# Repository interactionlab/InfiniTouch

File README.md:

# InfiniTouch: Finger-Aware Interaction on Fully Touch Sensitive Smartphones
This repository contains both the hardware models and specifications for the full-touch smartphone prototype presented in the paper, 
as well as scripts and the model for estimating 3D finger positions on the device as described in the paper. 
Moreover, our dataset can be downloaded in the link provided below.

## Abstract
Smartphones are the most successful mobile devices and offer intuitive interaction through touchscreens. Current devices
treat all fingers equally and only sense touch contacts on the front of the device. In this paper, we present InfiniTouch,
the first system that enables touch input on the whole device surface and identifies the fingers touching the device without
external sensors while keeping the form factor of a standard smartphone. We first developed a prototype with capacitive
sensors on the front, the back and on three sides. We then conducted a study to train a convolutional neural network that
identifies fingers with an accuracy of 95.78% while estimating their position with a mean absolute error of 0.74cm . We
demonstrate the usefulness of multiple use cases made possible with InfiniTouch, including finger-aware gestures and finger
flexion state as an action modifier.

This work can be cited as follows:
<pre>
@inproceedings{le2018infinitouch,
 author = {Le, Huy Viet and  Mayer, Sven and Henze, Niels},
 title = {InfiniTouch: Finger-Aware Interaction on Fully Touch Sensitive Smartphones},
 booktitle = {Proceedings of the 31th Annual ACM Symposium on User Interface Software and Technology},
 series = {UIST '18},
 year = {2018},
 isbn = {978-1-4503-5948-1},
 doi = {10.1145/3242587.3242605},
 url = {http://doi.acm.org/10.1145/3242587.3242605},
 location = {Berlin, Germany},
 numpages = {14},
 publisher = {ACM},
 address = {New York, NY, USA}
} 
</pre>

## Dataset
The dataset can be downloaded at: https://www.dropbox.com/s/v8n8uaf5vncusyn/InfiniTouch_Dataset.zip?dl=0. After downloading, place the content of this folder into a folder named 'data'. Place the 'data' folder into the same directory as the Jupyter notebooks. Run the content of these notebooks to create a HDF5 file with which the model can then be trained.

## Prototype
The datasheets of the components that we used in our prototype can be found in the following list of URLs:
- BM10NB(0.8)-40DS-0.4V(51): https://www.datasheets360.com/part/detail/bm10nb-0-8-40ds-0-4v-51/2579290684464631510/
- BM10B(0.8)-40DP-0.4V(51): https://www.datasheets360.com/part/detail/bm10b-0-8-40dp-0-4v-51/-1995328425388918022/
- MPR121QR2: https://www.datasheets360.com/part/detail/mpr121qr2/3714073967749496703/
- MicroUSB Breakout Board: https://cdn-shop.adafruit.com/datasheets/1833_MicroB_20329.pdf
- Tactile Switch: https://cdn-shop.adafruit.com/datasheets/B3F-1000-Omron.pdf
- FH12-50S-0.5SH(05): https://www.datasheets360.com/part/detail/fh12-50s-0-5sh-05/8224149447061018923/
- PCB board + FFC cable: http://diy.shops.hypeltd.com/DIY2//product_info.php?products_id=67

We printed the PCB and placed the components on the board with the service of http://beta-layout.com.

## Android Library
To use the library, include libftsp.jar in your Android project. The capacitive images for the local device can be accessed as follows:
```java
LocalDeviceHandler localDeviceHandler = new LocalDeviceHandler();
localDeviceHandler.setLocalCapImgListener(new LocalCapImgListener() {
    @Override
    public void onLocalCapImg(CapacitiveImageTS capImg) { // called approximately every 50ms
        int[][] matrix = capImg.getMatrix(); // get the 27x15 capacitive image
        int[] flattenedMatrix = capImg.getFlattenedMatrix(); // get a flattened 27x15 capacitive image
        long imgTimestamp = capImg.getTimestamp(); // get timestamp of this image
    }
});
localDeviceHandler.startHandler();
```

The following code is for the front unit. It provides the capacitive images of the front device (local) and further the retrieved capacitive imags of the back and the sides. All capacitive images can be retrieved within callbacks:

```java
try {
    frontDeviceHandler = new FrontDeviceHandler(9584);
} catch (SocketException e) {
    e.printStackTrace();
}

frontDeviceHandler.setFtspCapImgListener(new FTSPCapImgListener() {
    @Override
    public void onNewBackCapacitiveImage(CapacitiveImageTS capacitiveImageTS) {
        // backImage = capacitiveImageTS;
    }

    @Override
    public void onNewFrontCapacitiveImage(CapacitiveImageTS capacitiveImageTS) {
        // frontImage = capacitiveImageTS;
    }

    @Override
    public void onNewSideCapacitiveImage(CapacitiveImageSide capacitiveImageSide) {
        // sideImage = capacitiveImageSide;
    }
});
frontDeviceHandler.startHandler(true);
```

The back unit uses the respective code to broadcast the capacitive images to the front unit. A callback handler can also be added if required.
```java
backDeviceHandler = new BackDeviceHandler(Constants.FRONT_IP, 9584);
backDeviceHandler.startHandler(true);
```

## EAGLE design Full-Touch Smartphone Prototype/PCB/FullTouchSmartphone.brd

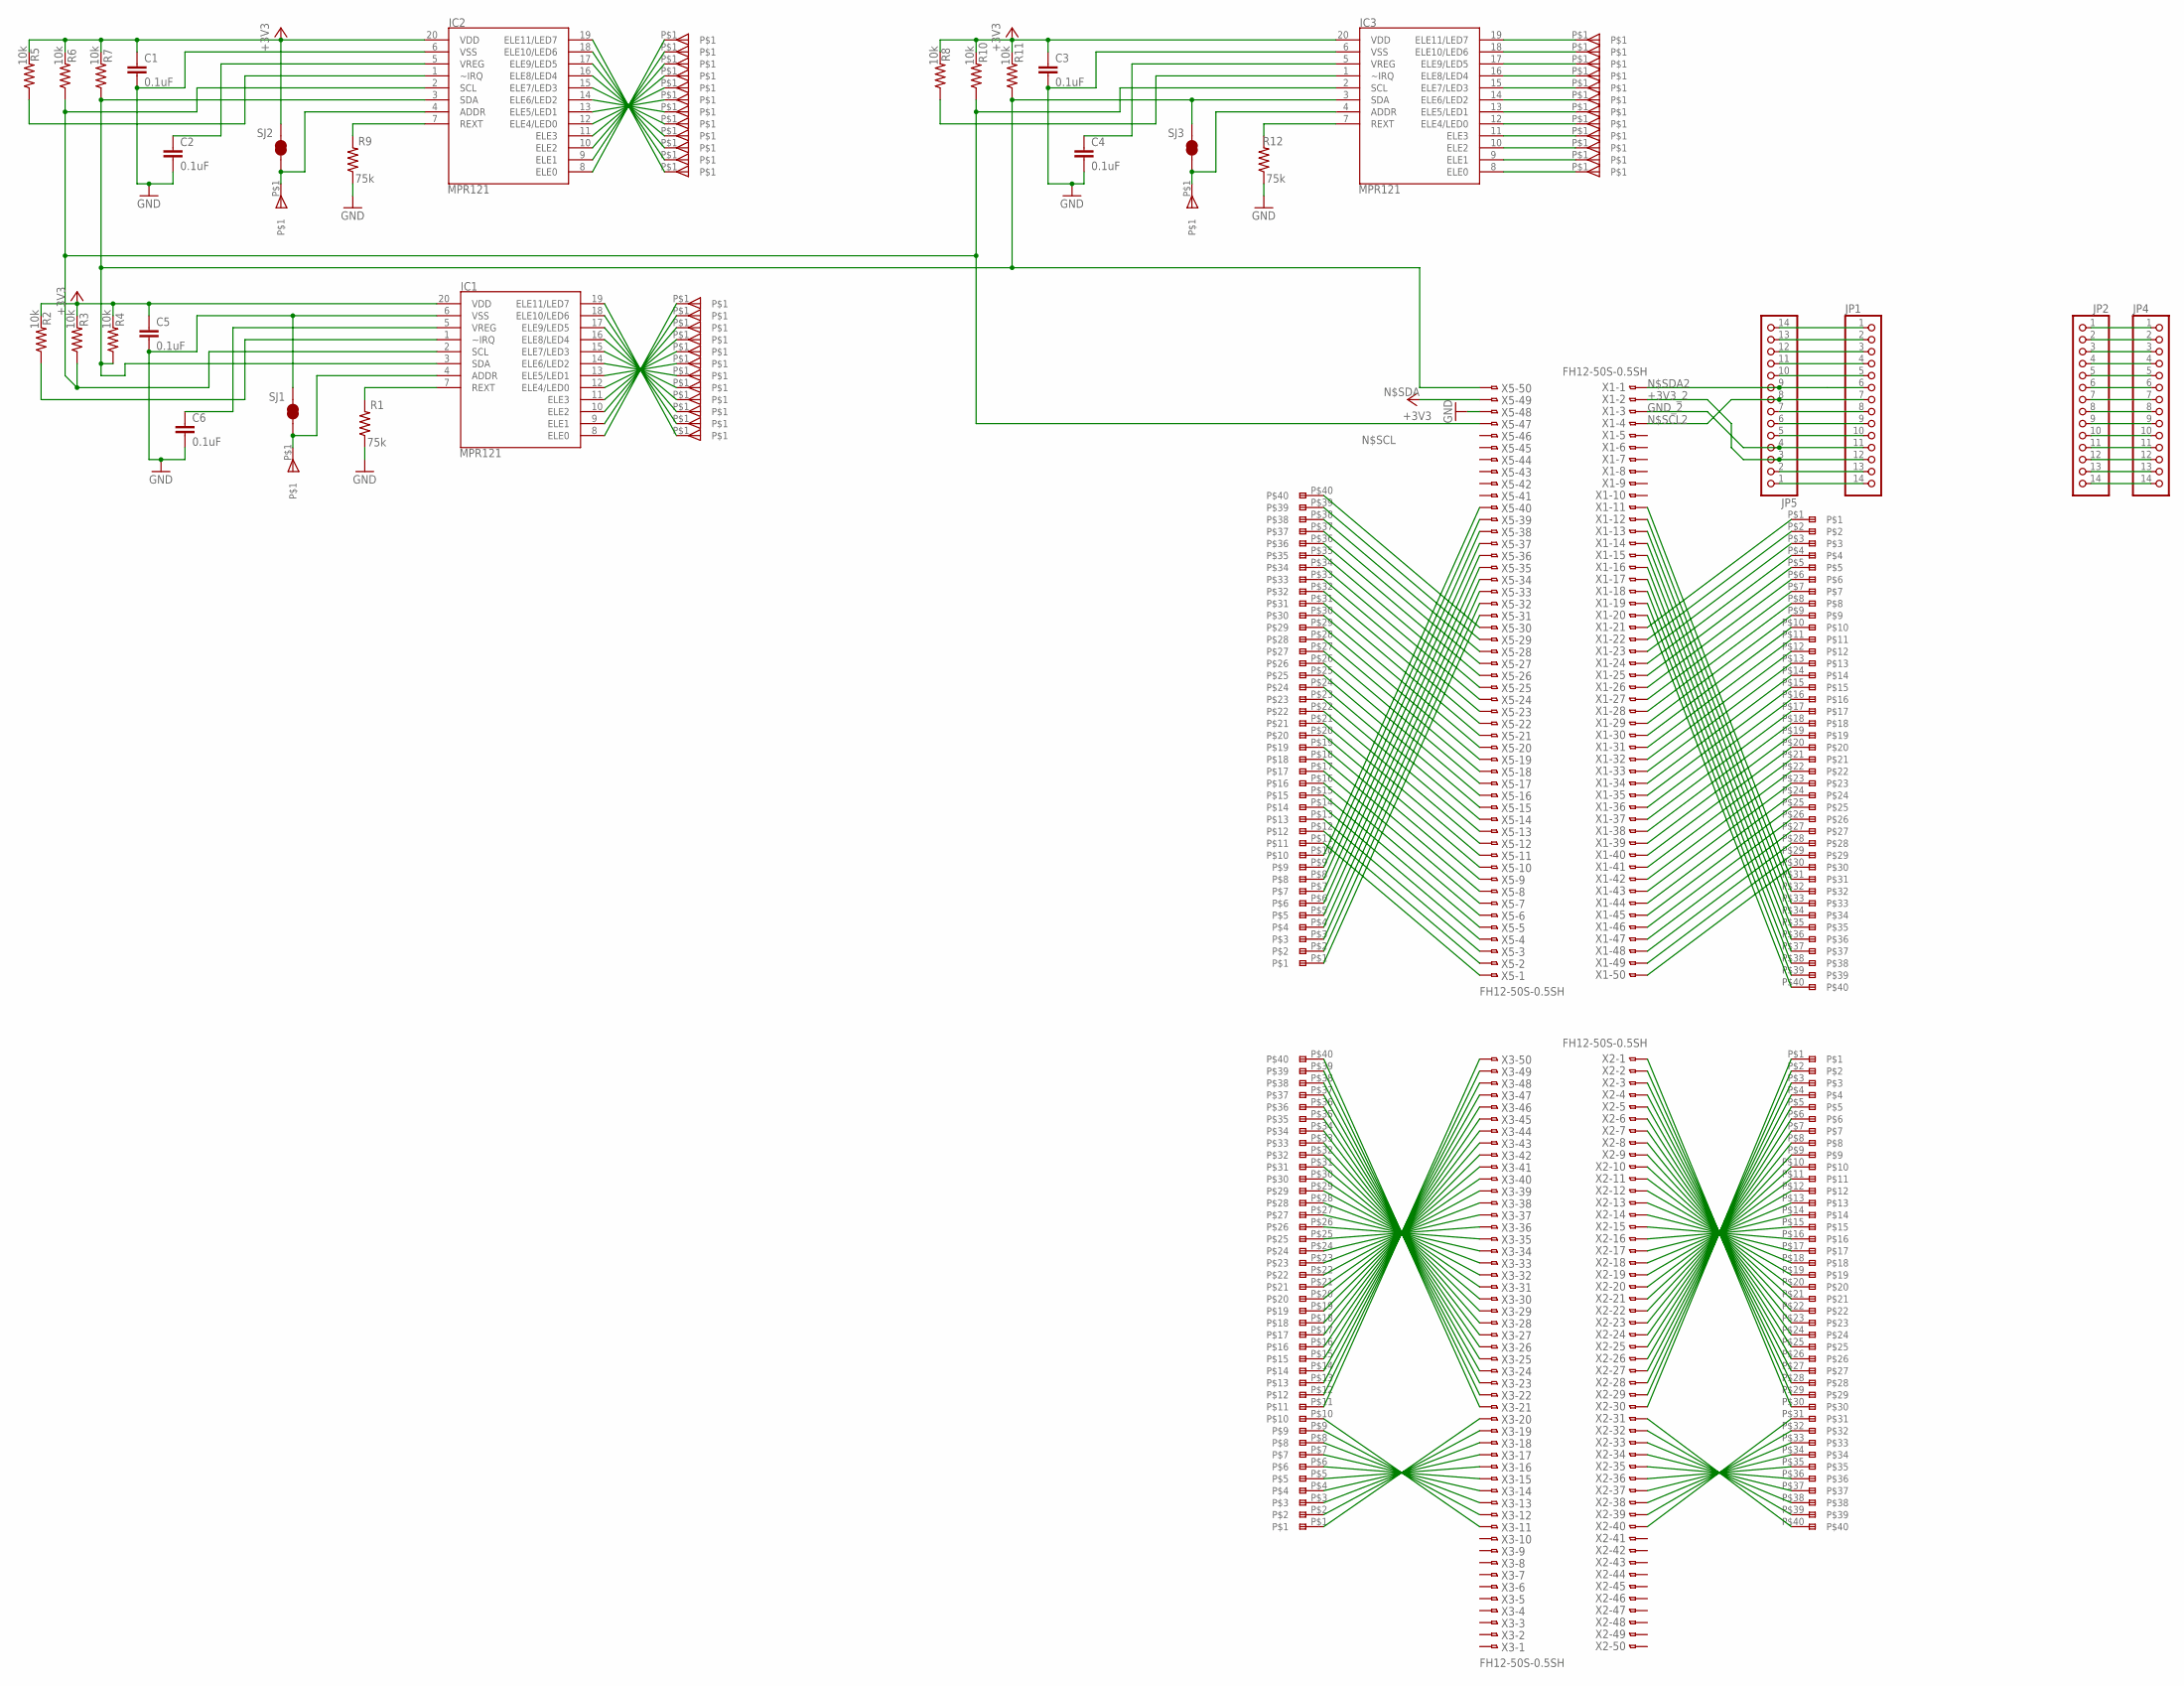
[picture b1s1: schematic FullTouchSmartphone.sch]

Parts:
C1, C2, C3, C4, C5, C6: 0.1uF; 0603-CAP
IC1, IC2, IC3: MPR121; QFN-20-0.4MM-V2
JP1, JP2, JP4, JP5: PINHD-1X14; 1X14
R1, R9, R12: 75k; 0603-RES
R2, R3, R4, R5, R6, R7, R8, R10, R11: 10k; 0603-RES
SJ1, SJ2, SJ3: SOLDERJUMPERTRACE; SJ_2S-TRACE
U$1, U$2: AXE640124
U$3, U$40PIN-BACK: AXE540127
U$4, U$5, U$6, U$7, U$8, U$9, U$10, U$11, U$12, U$13, U$14, U$15, U$25, U$26, U$27, U$28, U$29, U$30, U$31, U$32, U$33, U$34, U$35, U$36, U$37, U$38, U$39, U$40, U$41, U$42, U$43, U$44, U$45, U$46, U$47, U$48, U$49, U$50, U$51: SINGLE_LÖT_SPOT_K
X1, X2, X3, X5: FH12-50S-0.5SH

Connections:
+3V3: C1.1, C3.1, C5.1, IC1.20 (VDD), IC2.20 (VDD), IC3.20 (VDD), R2.2, R3.2, R4.2, R5.2, R6.2, R7.2, R8.2, R10.2, R11.2, SJ2.2, X5.49
+3V3_2: JP1.12, JP5.3, X1.2
GND: C1.2, C2.2, C3.2, C4.2, C5.2, C6.2, IC1.6 (VSS), IC2.6 (VSS), IC3.6 (VSS), R1.1, R9.1, R12.1, SJ1.2, X5.48
GND_2: JP1.11, JP5.4, X1.3
unnamed: U$40PIN-BACK.P$10, X5.40
unnamed: U$40PIN-BACK.P$9, X5.39
unnamed: U$40PIN-BACK.P$8, X5.38
unnamed: U$40PIN-BACK.P$7, X5.37
unnamed: U$40PIN-BACK.P$6, X5.36
unnamed: U$40PIN-BACK.P$5, X5.35
unnamed: U$40PIN-BACK.P$4, X5.34
unnamed: U$40PIN-BACK.P$3, X5.33
unnamed: U$40PIN-BACK.P$2, X5.32
unnamed: U$40PIN-BACK.P$1, X5.31
unnamed: U$40PIN-BACK.P$20, X5.10
unnamed: U$40PIN-BACK.P$19, X5.9
unnamed: U$40PIN-BACK.P$18, X5.8
unnamed: U$40PIN-BACK.P$17, X5.7
unnamed: U$40PIN-BACK.P$16, X5.6
unnamed: U$40PIN-BACK.P$15, X5.5
unnamed: U$40PIN-BACK.P$14, X5.4
unnamed: U$40PIN-BACK.P$13, X5.3
unnamed: U$40PIN-BACK.P$12, X5.2
unnamed: U$40PIN-BACK.P$11, X5.1
unnamed: U$40PIN-BACK.P$40, X5.30
unnamed: U$40PIN-BACK.P$39, X5.29
unnamed: U$40PIN-BACK.P$38, X5.28
unnamed: U$40PIN-BACK.P$37, X5.27
unnamed: U$40PIN-BACK.P$36, X5.26
unnamed: U$40PIN-BACK.P$35, X5.25
unnamed: U$40PIN-BACK.P$33, X5.23
unnamed: U$40PIN-BACK.P$34, X5.24
unnamed: U$40PIN-BACK.P$32, X5.22
unnamed: U$40PIN-BACK.P$31, X5.21
unnamed: U$40PIN-BACK.P$30, X5.20
unnamed: U$40PIN-BACK.P$29, X5.19
unnamed: U$40PIN-BACK.P$28, X5.18
unnamed: U$40PIN-BACK.P$27, X5.17
unnamed: U$40PIN-BACK.P$26, X5.16
unnamed: U$40PIN-BACK.P$25, X5.15
unnamed: U$40PIN-BACK.P$24, X5.14
unnamed: U$40PIN-BACK.P$23, X5.13
unnamed: U$40PIN-BACK.P$22, X5.12
unnamed: U$40PIN-BACK.P$21, X5.11
unnamed: U$2.P$31, X1.11
unnamed: U$2.P$30, X1.50
unnamed: U$2.P$29, X1.49
unnamed: U$2.P$28, X1.48
unnamed: U$2.P$27, X1.47
unnamed: U$2.P$26, X1.46
unnamed: U$2.P$25, X1.45
unnamed: U$2.P$24, X1.44
unnamed: U$2.P$23, X1.43
unnamed: U$2.P$21, X1.41
unnamed: U$2.P$22, X1.42
unnamed: U$2.P$20, X1.40
unnamed: U$2.P$19, X1.39
unnamed: U$2.P$18, X1.38
unnamed: U$2.P$17, X1.37
unnamed: U$2.P$15, X1.35
unnamed: U$2.P$16, X1.36
unnamed: U$2.P$14, X1.34
unnamed: U$2.P$13, X1.33
unnamed: U$2.P$12, X1.32
unnamed: U$2.P$11, X1.31
unnamed: U$2.P$10, X1.30
unnamed: U$2.P$9, X1.29
unnamed: U$2.P$8, X1.28
unnamed: U$2.P$7, X1.27
unnamed: U$2.P$6, X1.26
unnamed: U$2.P$5, X1.25
unnamed: U$2.P$4, X1.24
unnamed: U$2.P$3, X1.23
unnamed: U$2.P$2, X1.22
unnamed: U$2.P$1, X1.21
unnamed: U$2.P$32, X1.12
unnamed: U$2.P$33, X1.13
unnamed: U$2.P$34, X1.14
unnamed: U$2.P$35, X1.15
unnamed: U$2.P$36, X1.16
unnamed: U$2.P$37, X1.17
unnamed: U$2.P$38, X1.18
unnamed: U$2.P$39, X1.19
unnamed: U$2.P$40, X1.20
unnamed: U$3.P$20, X3.41
unnamed: U$3.P$11, X3.50
unnamed: U$3.P$21, X3.40
unnamed: U$3.P$22, X3.39
unnamed: U$3.P$23, X3.38
unnamed: U$3.P$24, X3.37
unnamed: U$3.P$25, X3.36
unnamed: U$3.P$26, X3.35
unnamed: U$3.P$27, X3.34
unnamed: U$3.P$28, X3.33
unnamed: U$3.P$29, X3.32
unnamed: U$3.P$30, X3.31
unnamed: U$3.P$31, X3.30
unnamed: U$3.P$32, X3.29
unnamed: U$3.P$33, X3.28
unnamed: U$3.P$34, X3.27
unnamed: U$3.P$35, X3.26
unnamed: U$3.P$36, X3.25
unnamed: U$3.P$37, X3.24
unnamed: U$3.P$38, X3.23
unnamed: U$3.P$39, X3.22
unnamed: U$3.P$40, X3.21
unnamed: U$3.P$19, X3.42
unnamed: U$3.P$18, X3.43
unnamed: U$3.P$17, X3.44
unnamed: U$3.P$16, X3.45
unnamed: U$3.P$15, X3.46
unnamed: U$3.P$14, X3.47
unnamed: U$3.P$13, X3.48
unnamed: U$3.P$12, X3.49
unnamed: U$3.P$1, X3.20
unnamed: U$3.P$2, X3.19
unnamed: U$3.P$3, X3.18
unnamed: U$3.P$4, X3.17
unnamed: U$3.P$5, X3.16
unnamed: U$3.P$6, X3.15
unnamed: U$3.P$7, X3.14
unnamed: U$3.P$8, X3.13
unnamed: U$3.P$9, X3.12
unnamed: U$3.P$10, X3.11
unnamed: U$1.P$31, X2.40
unnamed: U$1.P$32, X2.39
unnamed: U$1.P$33, X2.38
unnamed: U$1.P$34, X2.37
unnamed: U$1.P$35, X2.36
unnamed: U$1.P$36, X2.35
unnamed: U$1.P$37, X2.34
unnamed: U$1.P$38, X2.33
unnamed: U$1.P$39, X2.32
unnamed: U$1.P$40, X2.31
unnamed: U$1.P$30, X2.1
unnamed: U$1.P$29, X2.2
unnamed: U$1.P$28, X2.3
unnamed: U$1.P$27, X2.4
unnamed: U$1.P$26, X2.5
unnamed: U$1.P$25, X2.6
unnamed: U$1.P$24, X2.7
unnamed: U$1.P$23, X2.8
unnamed: U$1.P$22, X2.9
unnamed: U$1.P$21, X2.10
unnamed: U$1.P$20, X2.11
unnamed: U$1.P$19, X2.12
unnamed: U$1.P$18, X2.13
unnamed: U$1.P$17, X2.14
unnamed: U$1.P$16, X2.15
unnamed: U$1.P$15, X2.16
unnamed: U$1.P$14, X2.17
unnamed: U$1.P$13, X2.18
unnamed: U$1.P$12, X2.19
unnamed: U$1.P$11, X2.20
unnamed: U$1.P$10, X2.21
unnamed: U$1.P$9, X2.22
unnamed: U$1.P$8, X2.23
unnamed: U$1.P$7, X2.24
unnamed: U$1.P$6, X2.25
unnamed: U$1.P$5, X2.26
unnamed: U$1.P$4, X2.27
unnamed: U$1.P$3, X2.28
unnamed: U$1.P$2, X2.29
unnamed: U$1.P$1, X2.30
unnamed: IC1.19 (ELE11/LED7), U$15.P$1
unnamed: IC1.18 (ELE10/LED6), U$14.P$1
unnamed: IC1.17 (ELE9/LED5), U$13.P$1
unnamed: IC1.16 (ELE8/LED4), U$12.P$1
unnamed: IC1.15 (ELE7/LED3), U$11.P$1
unnamed: IC1.14 (ELE6/LED2), U$10.P$1
unnamed: IC1.13 (ELE5/LED1), U$9.P$1
unnamed: IC1.12 (ELE4/LED0), U$8.P$1
unnamed: IC1.11 (ELE3), U$7.P$1
unnamed: IC1.10 (ELE2), U$6.P$1
unnamed: IC1.9 (ELE1), U$5.P$1
unnamed: IC1.8 (ELE0), U$4.P$1
unnamed: IC3.19 (ELE11/LED7), U$40.P$1
unnamed: IC3.18 (ELE10/LED6), U$41.P$1
unnamed: IC3.17 (ELE9/LED5), U$42.P$1
unnamed: IC3.16 (ELE8/LED4), U$43.P$1
unnamed: IC3.15 (ELE7/LED3), U$44.P$1
unnamed: IC3.14 (ELE6/LED2), U$45.P$1
unnamed: IC3.13 (ELE5/LED1), U$46.P$1
unnamed: IC3.12 (ELE4/LED0), U$47.P$1
unnamed: IC3.10 (ELE2), U$49.P$1
unnamed: IC3.11 (ELE3), U$48.P$1
unnamed: IC3.9 (ELE1), U$50.P$1
unnamed: IC3.8 (ELE0), U$51.P$1
unnamed: JP2.1, JP4.1
unnamed: JP2.2, JP4.2
unnamed: C6.1, IC1.5 (VREG)
unnamed: C2.1, IC2.5 (VREG)
unnamed: IC1.7 (REXT), R1.2
unnamed: IC2.8 (ELE0), U$36.P$1
unnamed: IC2.9 (ELE1), U$35.P$1
unnamed: C4.1, IC3.5 (VREG)
unnamed: IC2.10 (ELE2), U$34.P$1
unnamed: IC2.11 (ELE3), U$33.P$1
unnamed: IC2.12 (ELE4/LED0), U$32.P$1
unnamed: IC2.13 (ELE5/LED1), U$31.P$1
unnamed: IC2.14 (ELE6/LED2), U$30.P$1
unnamed: IC2.15 (ELE7/LED3), U$29.P$1
unnamed: IC2.16 (ELE8/LED4), U$28.P$1
unnamed: IC2.17 (ELE9/LED5), U$27.P$1
unnamed: IC2.18 (ELE10/LED6), U$26.P$1
unnamed: IC2.19 (ELE11/LED7), U$25.P$1
unnamed: IC1.4 (ADDR), SJ1.1, U$37.P$1
unnamed: IC2.7 (REXT), R9.2
unnamed: IC3.7 (REXT), R12.2
unnamed: IC2.4 (ADDR), SJ2.1, U$38.P$1
unnamed: IC3.4 (ADDR), SJ3.1, U$39.P$1
unnamed: JP2.3, JP4.3
unnamed: JP2.4, JP4.4
unnamed: JP2.5, JP4.5
unnamed: JP2.6, JP4.6
unnamed: JP2.7, JP4.7
unnamed: JP2.8, JP4.8
unnamed: JP2.9, JP4.9
unnamed: JP2.10, JP4.10
unnamed: JP2.11, JP4.11
unnamed: JP2.12, JP4.12
unnamed: JP2.13, JP4.13
unnamed: JP2.14, JP4.14
unnamed: JP1.1, JP5.14
unnamed: JP1.2, JP5.13
unnamed: JP1.3, JP5.12
unnamed: JP1.4, JP5.11
unnamed: JP1.5, JP5.10
unnamed: JP1.8, JP5.7
unnamed: JP1.9, JP5.6
unnamed: JP1.10, JP5.5
unnamed: JP1.13, JP5.2
unnamed: JP1.14, JP5.1
N$IRQ1: IC1.1 (~IRQ), R2.1
N$IRQ2: IC2.1 (~IRQ), R5.1
N$IRQ3: IC3.1 (~IRQ), R8.1
N$SCL: IC1.2 (SCL), IC2.2 (SCL), IC3.2 (SCL), R3.1, R6.1, R10.1, X5.47
N$SCL2: JP1.7, JP5.8, X1.4
N$SDA: IC1.3 (SDA), IC2.3 (SDA), IC3.3 (SDA), R4.1, R7.1, R11.1, SJ3.2, X5.50
N$SDA2: JP1.6, JP5.9, X1.1

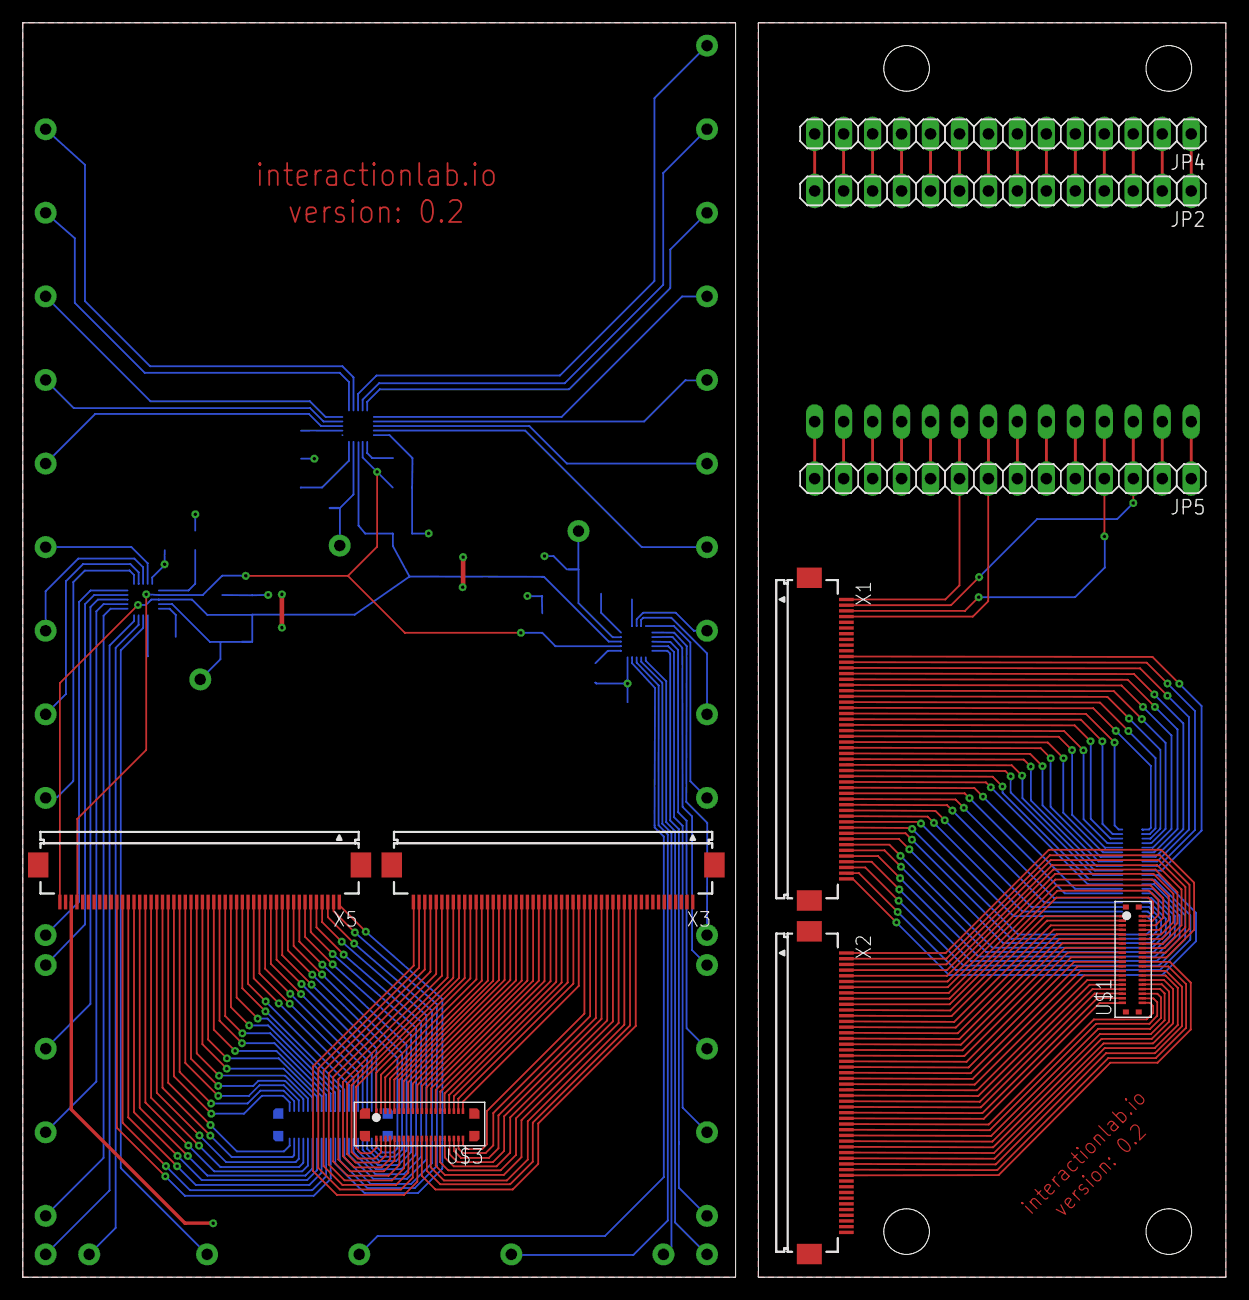
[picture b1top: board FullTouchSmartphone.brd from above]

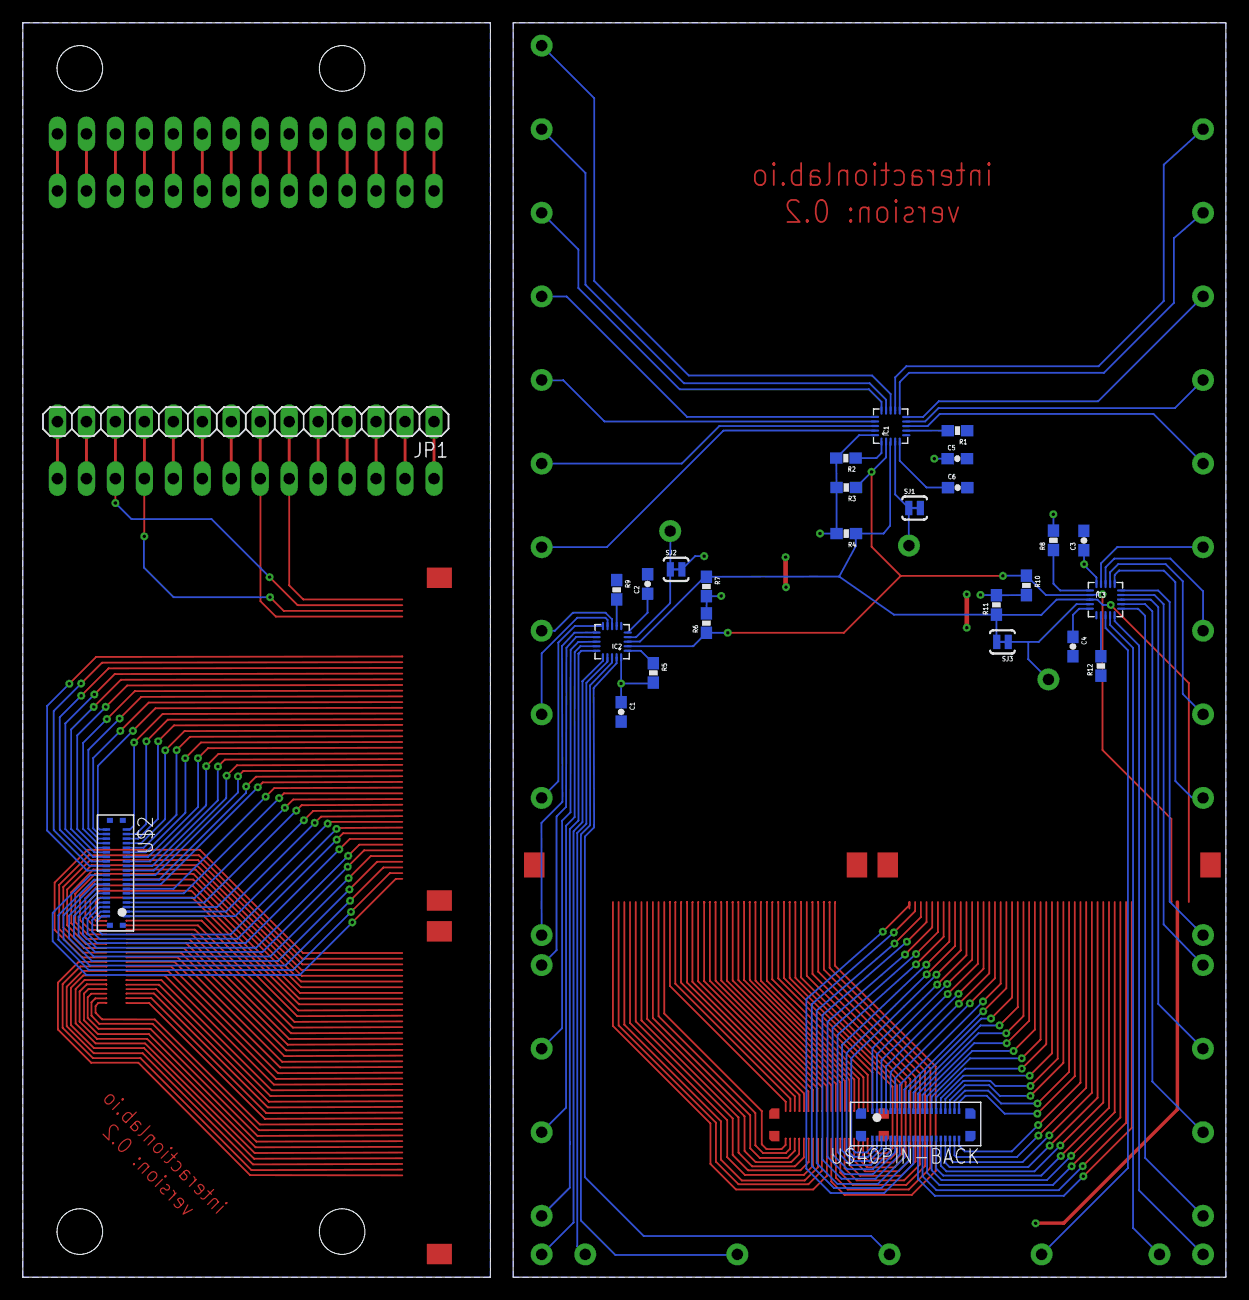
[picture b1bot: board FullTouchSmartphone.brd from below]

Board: 2 copper layers, 105.5 x 110.0 mm, 75 parts (27 on the bottom side), 240 nets.

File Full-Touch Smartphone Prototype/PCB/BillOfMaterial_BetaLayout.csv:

"BILL OF MATERIAL WITH BETA STOCK, GROUPED BY VALUES, AS OF 09.10.2015"
"Part","Value","Device","Package","Description","Description2","Qty","Place_YES/NO","Povided_by_customer_YES/NO","Distributor","Ordernumber","Weblink","Remarks_customer","Unit_price","Total_price","REMARKS_BETA","OPTION1","OPTION2","OPTION3"
"C1, C2, C3, C4, C5, C6","0.1uF","CAP0603-CAP","0603-CAP","Capacitor"," ","6","YES","NO","Mouser","581-06033C104JAT2A","http://www.mouser.de/ProductDetail/AVX/06033C104JAT2A/?qs=9m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"," ","0.292","1.752"," "," "," "," "
"IC1, IC2, IC3","MPR121","MPR121V2","QFN-20-0.4MM-V2","MPR121 Capacitive Touch Sensor Controller. Variant V2"" was created using an image import of the bottom of the IC. It matches metal to metal."""," ","3","YES","YES","-"," "," "," "," "," "," "," "," "," "
"JP1, JP2, JP4, JP5"," ","PINHD-1X14","1X14","PIN HEADER"," ","4","NO","NO","-","-","-"," ","-","-"," "," "," "," "
"R1, R9, R12","75k","RESISTOR0603-RES","0603-RES","Resistor"," ","3","YES","NO","Mouser","603-RT0603FRE0775KL","http://www.mouser.de/ProductDetail/Yageo/RT0603FRE0775KL/?qs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"," ","0.179","0.537"," "," "," "," "
"R2, R3, R4, R5, R6, R7, R8, R10, R11","10k","RESISTOR0603-RES","0603-RES","Resistor"," ","9","YES","NO","Mouser","652-CRT0603BY1002EAS","http://www.mouser.de/ProductDetail/Bourns/CRT0603-BY-1002EAS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"," ","0.521","4.689"," "," "," "," "
"SJ1, SJ2, SJ3","SOLDERJUMPERTRACE","SOLDERJUMPERTRACE","SJ_2S-TRACE","Solder Jumper"," ","3"," "," "," "," "," "," "," "," "," "," "," "," "
"U$1, U$2","AXE640124","AXE640124","AXE640124","Board to Board & Mezzanine Connectors 0.4MM FPC TO BOARD 40P HDR 0.8 HGHT"," ","2","YES","NO","Mouser","798-BM10B0840DP04V51","http://www.mouser.de/ProductDetail/Hirose-Connector/BM10B08-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"," ","0.952","1.904"," "," "," "," "
"U$3, U$40PIN-BACK","AXE540127","AXE540127","AXE540127","Board to Board & Mezzanine Connectors 0.4MM FPC TO BOARD 40P RECP 0.8 HGHT"," ","2","YES","NO","Mouser","798-BM10NB0840DS4V51","http://www.mouser.de/ProductDetail/Hirose-Connector/BM10NB08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"," ","1.2","2.4"," "," "," "," "
"U$4, U$5, U$6, U$7, U$8, U$9, U$10, U$11, U$12, U$13, U$14, U$15, U$25, U$26, U$27, U$28, U$29, U$30, U$31, U$32, U$33, U$34, U$35, U$36, U$37, U$38, U$39, U$40, U$41, U$42, U$43, U$44, U$45, U$46, U$47, U$48, U$49, U$50, U$51","SINGLE_LÖT_SPOT_K","SINGLE_LÖT_SPOT_K","SINGLE_LÖT_SPOT_K"," "," ","39"," "," "," "," "," "," "," "," "," "," "," "," "
"X1, X2, X3, X5","FH12-50S-0.5SH","FH12-50S-0.5SH","FH12-50S-0.5SH","0.5mm Pitch Connectors For FPC/FFC"," ","4","YES","NO","Mouser","798-FH12-50S-0.5SH55","http://www.mouser.de/ProductDetail/Hirose-Connector/FH12-50S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"," ","3.29","13.16"," "," "," "," "

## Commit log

2018-07-16 Added first batch of files.
2018-07-16 Added Images.
2018-07-16 Added BillOfMaterial and Component Layout (can be re-used for Beta Layout)
2018-07-16 Added notebook for model training.
2018-07-16 Update.
2018-07-16 Added code examples to the readme
2018-07-16 Added Library
2018-07-16 Added Download Link for the Dataset
2018-08-10 Added modified kernel for the Nexus 5 which provides the capacitive images.
2018-08-10 Fixed code examples.
2020-06-23 Added kernel variants.
